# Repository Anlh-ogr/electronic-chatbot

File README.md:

# electronic-chatbot
chatbot AI

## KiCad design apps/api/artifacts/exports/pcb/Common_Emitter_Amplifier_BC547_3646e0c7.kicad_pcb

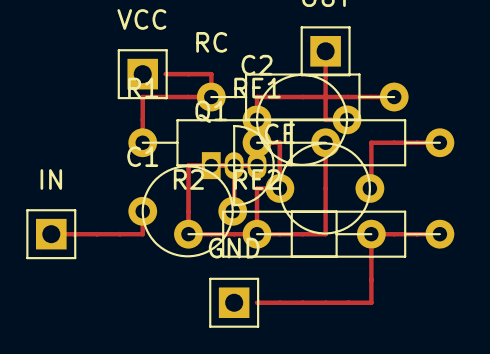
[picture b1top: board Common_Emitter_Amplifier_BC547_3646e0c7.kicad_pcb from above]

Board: 2 copper layers, 13 parts (0 on the bottom side), 8 nets.

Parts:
C1, C2: CAPACITOR; C_Disc_D5.0mm
CE: CAPACITOR; C_Disc_D5.0mm
GND: POWER_SYMBOL; N/A
IN: CONNECTOR; PinHeader_1x01_P2.54mm_Vertical
OUT: CONNECTOR; PinHeader_1x01_P2.54mm_Vertical
Q1: BJT_NPN; TO-92_Inline
R1, R2: RESISTOR; R_Axial_DIN0207
RC: RESISTOR; R_Axial_DIN0207
RE1, RE2: RESISTOR; R_Axial_DIN0207
VCC: POWER_SYMBOL; N/A

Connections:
0: GND.1, R2.2, RE2.2
BASE: C1.2, Q1.2, R1.2, R2.1
COLLECTOR: C2.1, Q1.3, RC.2
EMITTER: CE.1, Q1.1, RE1.1, RE2.1
IN: C1.1, IN.1
OUT: C2.2, OUT.1
RE_GND: CE.2, RE1.2
VCC: R1.1, RC.1, VCC.1

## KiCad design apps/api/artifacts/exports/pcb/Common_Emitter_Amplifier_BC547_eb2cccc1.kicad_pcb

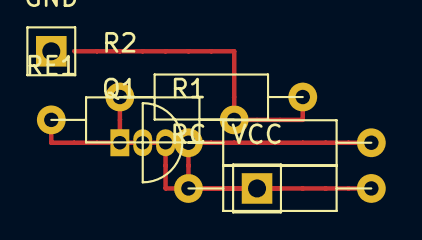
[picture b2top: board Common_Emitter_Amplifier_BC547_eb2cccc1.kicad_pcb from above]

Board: 2 copper layers, 7 parts (0 on the bottom side), 5 nets.

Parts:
GND: POWER_SYMBOL; None
Q1: BJT_NPN; TO-92_Inline
R1, R2: RESISTOR; R_Axial_DIN0207_L6.3mm_D2.5mm_P10.16mm_Horizontal
RC: RESISTOR; R_Axial_DIN0207_L6.3mm_D2.5mm_P10.16mm_Horizontal
RE1: RESISTOR; R_Axial_DIN0207_L6.3mm_D2.5mm_P10.16mm_Horizontal
VCC: POWER_SYMBOL; None

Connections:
0: GND.1, R2.2, RE1.2
BASE: Q1.2, R1.2, R2.1
COLLECTOR: Q1.3, RC.2
EMITTER: Q1.1, RE1.1
VCC: R1.1, RC.1, VCC.1

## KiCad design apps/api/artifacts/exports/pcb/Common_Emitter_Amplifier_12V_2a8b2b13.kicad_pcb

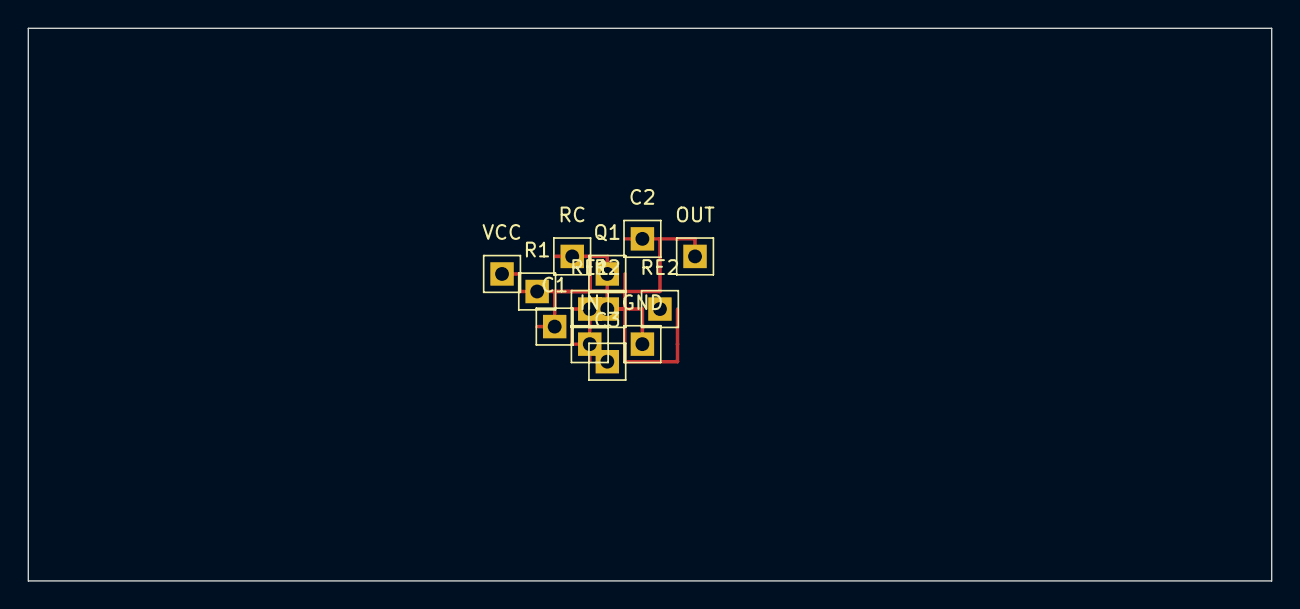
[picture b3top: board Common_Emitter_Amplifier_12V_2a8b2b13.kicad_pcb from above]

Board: 2 copper layers, 90.0 x 40.0 mm, 13 parts (0 on the bottom side), 4 nets.

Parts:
C1, C2, C3: CONNECTOR; PinHeader_1x01_P2.54mm_Vertical
GND: CONNECTOR; PinHeader_1x01_P2.54mm_Vertical
IN: CONNECTOR; PinHeader_1x01_P2.54mm_Vertical
OUT: CONNECTOR; PinHeader_1x01_P2.54mm_Vertical
Q1: CONNECTOR; PinHeader_1x01_P2.54mm_Vertical
R1, R2: CONNECTOR; PinHeader_1x01_P2.54mm_Vertical
RC: CONNECTOR; PinHeader_1x01_P2.54mm_Vertical
RE1, RE2: CONNECTOR; PinHeader_1x01_P2.54mm_Vertical
VCC: CONNECTOR; PinHeader_1x01_P2.54mm_Vertical

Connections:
BASE: R1.1, R2.1
IN: C1.1, IN.1
RE_NODE: C3.1, RE2.1
VCC: RC.1, VCC.1

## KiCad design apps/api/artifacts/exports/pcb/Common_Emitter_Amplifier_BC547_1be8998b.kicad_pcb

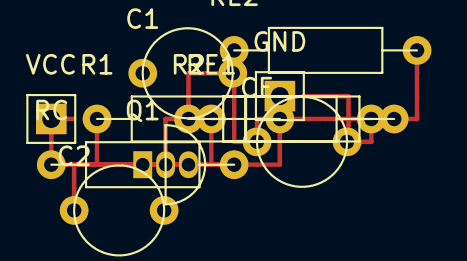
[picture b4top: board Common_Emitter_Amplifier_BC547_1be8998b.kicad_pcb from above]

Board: 2 copper layers, 11 parts (0 on the bottom side), 6 nets.

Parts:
C1, C2: CAPACITOR; C_Disc_D5.0mm
CE: CAPACITOR; C_Disc_D5.0mm
GND: POWER_SYMBOL; N/A
Q1: BJT_NPN; TO-92_Inline
R1, R2: RESISTOR; R_Axial_DIN0207
RC: RESISTOR; R_Axial_DIN0207
RE1, RE2: RESISTOR; R_Axial_DIN0207
VCC: POWER_SYMBOL; N/A

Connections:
0: CE.2, GND.1, R2.2, RE2.2
+12V: R1.2, RC.1, VCC.1
BASE: C1.2, Q1.2, R1.1, R2.1
COLLECTOR: C2.1, Q1.3, RC.2
EMITTER: Q1.1, RE1.1
RE_NODE: CE.1, RE1.2, RE2.1

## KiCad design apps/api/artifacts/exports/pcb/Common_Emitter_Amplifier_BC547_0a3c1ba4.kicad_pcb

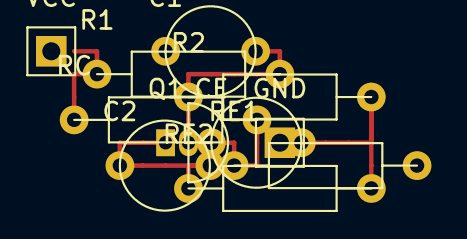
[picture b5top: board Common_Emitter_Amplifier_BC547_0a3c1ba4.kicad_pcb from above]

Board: 2 copper layers, 11 parts (0 on the bottom side), 5 nets.

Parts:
C1, C2: CAPACITOR; C_Disc_D5.0mm_W2.5mm_P5.00mm
CE: CAPACITOR; C_Disc_D5.0mm_W2.5mm_P5.00mm
GND: POWER_SYMBOL; N/A
Q1: BJT_NPN; TO-92_Inline
R1, R2: RESISTOR; R_Axial_DIN0207_L6.3mm_D2.5mm_P10.16mm_Horizontal
RC: RESISTOR; R_Axial_DIN0207_L6.3mm_D2.5mm_P10.16mm_Horizontal
RE1, RE2: RESISTOR; R_Axial_DIN0207_L6.3mm_D2.5mm_P10.16mm_Horizontal
VCC: POWER_SYMBOL; N/A

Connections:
0: CE.2, GND.1, R2.2, RE2.2
BASE: C1.2, Q1.2, R1.2, R2.1
COLLECTOR: C2.1, Q1.1, RC.2
EMITTER: CE.1, Q1.3, RE1.1, RE2.1
VCC: R1.1, RC.1, VCC.1

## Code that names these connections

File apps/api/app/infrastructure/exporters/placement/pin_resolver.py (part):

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#   Body half-length = 2.54 mm + 1 pin-stub (2.54 mm) → total = 5.08 mm
PIN_OFFSET: float = 2.0 * GRID_MM   # 5.08 mm (2 grid units)

# BJT pin distances:  base lateral (2 grid), collector/emitter vertical (2 grid)
BJT_BASE_OFFSET: float = 2.0 * GRID_MM   # 5.08 mm left for base
BJT_CE_OFFSET:   float = 2.0 * GRID_MM   # 5.08 mm up/down for C / E

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
def resolve_pins(comp_type: str, rotation: int = 0) -> Dict[str, Tuple[float, float]]:
    """Return pin offsets for a component type, applying rotation."""
    base = _fuzzy_pin_base(comp_type)
    if rotation % 360 == 0:
        return dict(base)
    return rotate_offsets(base, rotation)
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
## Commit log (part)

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2025-12-19 Refactor script to use CircuitStore default path
    Updated the script to instantiate CircuitStore without specifying a file path, relying on its default behavior. Also removed the unused variable 'db' for cleaner code.
2025-12-22 Add Pydantic schemas for chat request and response
    Introduces ChatRequest and ChatResponse models using Pydantic for validating and structuring chat API input and output data.
2025-12-23 Refactor chat endpoint and add circuits listing route
    Refactored the /chat endpoint to use CircuitStore directly, improved error handling, and clarified response structure. Added a new /circuits GET endpoint to list all circuits in the database.
2025-12-25 Refactor CircuitStore for improved clarity and config usage
    Refactored CircuitStore to use centralized config for the default database path, added type hints, improved comments, and enhanced metadata retrieval to include the 'project' field. The class now pro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
2025-12-29 Không commit file env.local
2025-12-30 Tạo một đầu nối API gọi các router từ thư mục
    Test với endpoind (health)
2026-01-07 Tập trung vào cấu trúc "Phân tầng Domain"
    Cập nhật định nghĩa Component, Net, Port và Constraint để phục vụ Rule Engine.
    Sử dụng Enums cho ComponentType và PortDirection để loại bỏ lỗi typo (magic strings).
    Triển khai phương thức with_component theo phong cách functional để hỗ trợ cập nhật mạch mà không thay đổi object cũ.
    Thêm ràng buộc kiểu dữ liệu ParameterValue để kiểm soát thông số linh kiện.
2026-01-11 Thêm tài liệu tổng quan hệ thống domain
    Bổ sung file docs/domain/tong-quan.md mô tả kiến trúc, điểm mạnh/yếu, quy trình kiểm thử, lộ trình phát triển và hướng dẫn sử dụng cho hệ thống domain circuits. Tài liệu giúp tổng hợp trạng thái hiện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
2026-01-11 Thêm tài liệu cho các thực thể domain mạch điện
    Giới thiệu một tài liệu Markdown chi tiết mô tả thiết kế, cấu trúc và logic kiểm định của tệp `entities.py` trong miền mạch điện. Tài liệu này bao gồm mục đích, mục tiêu, cấu trúc, vai trò và đánh gi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
2026-01-11 Thêm các bài kiểm tra toàn diện cho các mô-đun miền mạch
    Giới thiệu các bộ kiểm thử mới bao gồm các trường hợp ngoại lệ, tuần tự hóa/giải tuần tự hóa IR, đánh giá công cụ quy tắc và trình tạo mẫu tham số cho các thực thể mạch. Các bài kiểm thử này giúp tăn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
2026-01-19 thu vien hien thi mach kicanvas
    thu vien ho render tren web interface
2026-01-24 Mở rộng và làm rõ tài liệu IR cho lĩnh vực mạch điện
    Tài liệu IR (Intermediate Representation) cho lĩnh vực mạch điện đã được mở rộng và tái cấu trúc đáng kể.
    Bản cập nhật bổ sung các giải thích chi tiết về mục đích của IR, xác thực lược đồ, tính bất biến, kiểm thử khứ hồi và phân tách các mối quan tâm.
    Nó cũng bao gồm lý do kiến ​​trúc, điểm mạnh, hạn chế và các ví dụ sử dụng để cải thiện sự rõ ràng cho các nhà phát triển và người bảo trì.
2026-02-09 gỡ bản cũ
2026-02-11 Hỗ trợ kênh p và tái cấu trúc tính toán MOSFET
    Thêm hỗ trợ channel_type và tái cấu trúc các hàm hỗ trợ tính toán MOSFET.
    Giới thiệu MOSFETConfig.channel_type ("n"/"p"), thay đổi API MOSFETCalculator để trả về ParameterValue (có đơn vị) và chấp nhận ParameterValue cho đầu vào điện trở/tụ điện.
    Các phép tính hiện xử lý dấu/cực tính cho các thiết bị kênh p, sử dụng giá trị tuyệt đối để chuẩn hóa và mở rộng kiểm tra lỗi (kiểm tra tối thiểu VDS và xác thực độ lệch cổng).
    Đổi tên/tái cấu trúc logic xây dựng mạch (_create_nets -> _compute_values) để t
2026-02-18 Nâng cấp công cụ xử lý rules: mức độ nghiêm trọng & các hàm hỗ trợ
    Thêm các mức độ nghiêm trọng phong phú hơn và tái cấu trúc cơ sở hạ tầng quy tắc cơ bản để tăng tính mạnh mẽ và khả năng tái sử dụng.
    Mức độ nghiêm trọng của vi phạm (ViolationSeverity) có thêm mức ĐẠT THÀNH CÔNG (SUCCESS); Quy tắc mạch (CircuitRule) trở thành một quy tắc cơ bản trừu tượng (ABC) với cờ được bật, mô tả, validate_saf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
2026-02-22 sửa cmt
2026-03-11 cap nhat API
    Cập nhật tệp requirements.txt để sửa đổi các phụ thuộc API.
2026-03-12 Thêm các tệp siêu dữ liệu mẫu op-amp
    Thêm 13 tệp siêu dữ liệu op-amp mới (OP-01 đến OP-13) vào thư mục templates metadata.
    Mỗi tệp (metadata version v3.0.0) mô tả tham chiếu mẫu vật lý, phân loại miền (đảo, không đảo, vi sai; nguồn đơn/kép; tham chiếu AC/ảo/biến thể IO), cấu trúc chức năng (cổng, khối, công thức khuếch đ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
    Các mục siêu dữ liệu này cung cấp cho trình lập kế hoạch/giải quyết các chữ ký cấu trúc liên kết và gợi ý về kích th
2026-03-15 file init application
2026-03-19 Trình xác thực ràng buộc mạch
    Giới thiệu một Constraint Validator dựa trên quy tắc, có tính xác định để xác thực dữ liệu mạch được tạo ra.
    Thêm các lớp dữ liệu Violation và Validation Report và triển khai các kiểm tra cấu trúc, phạm vi tham số, khớp ý định và ràng buộc cứng (với mức độ nghiêm trọng lỗi/cảnh báo).
    Bao gồm các phạm vi tham số được xác định trước cho các thành phần phổ biến (điện trở, tụ điện, cuộn cảm, nguồn điện áp), tổng hợp các vi phạm và checked_rules, và trả về ValidationReport đạt/không đ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
    Được thiết k
2026-03-20 Tái cấu trúc bộ định tuyến LLM cho Google Cloud Gemini
    Tái cấu trúc lớn bộ định tuyến LLM: hợp nhất các vai trò thành một vai trò CHUNG, đơn giản hóa việc xử lý chế độ (AIR/PRO) và làm cho bộ định tuyến tập trung vào Gemini/Google Cloud.
    Thay thế mã và máy khách dành riêng cho Groq bằng logic tập trung vào GoogleCloud/Gemini, cập nhật việc phân giải biến môi trường (chấp nhận Google_Cloud_API_Key / GOOGLE_CLOUD_API_KEY / GEMINI_API_K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
    Hợp lý hóa việc xây dựng cấu h
2026-03-20 Thêm GenerateCircuitUseCase để tạo mẫu mạch
    Giới thiệu một trường hợp sử dụng mới để tạo mạch từ các mẫu.
    Thêm GenerateCircuitUseCase điều phối việc tải mẫu, xác thực tham số (ParameterValidator), ánh xạ tham số sang thành phần, xây dựng mạch thông qua TemplatesLoader, lưu trữ tùy chọn thông qua CircuitR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
    Đồng thời thêm enum TopologyType, xử lý lỗi mạnh mẽ (TemplateGenerationError) và chuyển đổi sang DTO CircuitResponse với siêu dữ liệu và thẻ.
    Hỗ trợ tìm kiếm mẫu gần đúng, cảnh báo về các vấ
2026-03-21 Thêm trình ánh xạ CircuitSpec
    Giới thiệu CircuitSpecMapper để chuyển đổi JSON CircuitSpec thành các thực thể Circuit trong miền và ngược lại.
    Thêm các hàm from_json/from_file/to_json và các hàm hỗ trợ để ánh xạ các thành phần, tham số, mạng và cổng, với chức năng xác thực, chuyển đổi kiểu (ComponentType, PortDirection), phân tích cú pháp P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
    Khóa các thành phần/mạng/cổng vào các từ điển thân thiện với miền và tuần tự hóa các thực thể thành JSON đặc tả.
2026-03-21 Xuất XGBoostTopologySelector trong gói ai_core
    Nhập XGBoostTopologySelector trong apps/api/app/domains/circuits/ai_core/__init__.py và thêm nó vào __all__ để bộ chọn được xuất công khai từ gói ai_core cho mục đích sử dụng bên ngoài.
2026-03-21 Trình kết xuất SVG cho KiCad CLI
    Giới thiệu KiCadCLIRenderer để kết xuất sơ đồ/PCB KiCad sang SVG bằng công cụ kicad-cli.
    Cung cấp các phương thức kết xuất bất đồng bộ và đồng bộ (render_to_svg / render_to_svg_sync), tìm kiếm các vị trí cài đặt phổ biến hoặc PATH cho kicad-cli, quản lý thư mục đầu ra, ghi nhật ký thực t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
    Được thiết kế như một phương án dự phòng phía máy chủ khi API KiCad trực tiếp hoặc kết xuất trình duyệt không khả dụng; yêu cầu kicad-cli phải được cài đặt trê
2026-03-21 Thêm kho lưu trữ mạch trong bộ nhớ
    Giới thiệu InMemoryCircuitRepository triển khai CircuitRepositoryPort (apps/api/.../circuits_repo_memory.py).
    Lưu trữ các thực thể Mạch trong một từ điển với các phương thức bất đồng bộ: lưu (tạo UUID nếu thiếu), lấy, liệt kê (hỗ trợ lọc tên đơn giản, phân trang và sắp xếp cơ bản), cập nhật, xóa, đếm và xóa 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
    Dành cho phát triển, thử nghiệm và MVP (không dành cho sản xuất); sử dụng ghi nhật ký và các phần giữ chỗ cho các cải tiến khóa/siêu dữ liệu trong tương lai.
2026-03-21 Khởi tạo ứng dụng FastAPI, thêm các tuyến routes
    Tái cấu trúc điểm vào chính của FastAPI: mở rộng chuỗi tài liệu mô-đun, thêm/nhập các bộ định tuyến cho chatbot, mạch và ảnh chụp nhanh, và đăng ký chúng trên ứng dụng.
    Giới thiệu SafeStaticFiles để trả về lỗi 404 cho các tệp tĩnh bị thiếu thay vì lỗi 500. Thêm các điểm cuối đơn giản: /api/health (kiểm tra trạng thái), / (phục vụ trang index.html phía giao diện ngườ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
    Đồng thời điều chỉnh các phần nhập
2026-03-21 Thêm mã JavaScript giao diện người dùng chatbot cho trợ lý mạch điện
    Giới thiệu một tập lệnh giao diện người dùng mới apps/api/static/js/chatbot.js triển khai giao diện người dùng và logic của Chatbot mạch điện tử.
    Các tính năng bao gồm: xử lý tin nhắn trò chuyện, kiểm tra trạng thái API, gửi/truyền yêu cầu mô phỏng (/api/chat, /api/chat/simulate/stream), phân tích luồng kiểu SSE, xây dựng danh sách mạng từ dữ 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
2026-03-22 NLU: phân tích độ khuếch đại, trở kháng đầu ra, ghép nối trực tiếp
    Cải thiện khả năng phân tích cú pháp của NLUService để phát hiện các yêu cầu bổ sung từ văn bản người dùng.
    Thêm các mẫu output_buffer bổ sung (các cụm từ trở kháng đầu ra thấp bằng tiếng Việt và tiếng Anh).
    Triển khai phân tích phạm vi độ khuếch đại (ví dụ: "gain 20-30", các biến thể tiếng Việt) và lưu trữ gain_min/gain_max.
    Thêm phân tích giới hạn trở kháng đầu ra (zout/trở kháng đầu ra) và lưu trữ output_impedance_max_ohm.
    Thêm tính năng phát hiện yêu cầu bắt buộc về g
2026-03-22 Sử dụng hình ảnh avatar bot
    Thay thế biểu tượng robot Font Awesome bằng hình ảnh tùy chỉnh cho avatar bot trong giao diện người dùng chatbot.
    Thay đổi này sẽ hoán đổi `<i class="fas fa-robot"></i>` với `<img src="/static/logo/System-icon.png" alt="Bot Avatar">` trong addMessage và chỉ báo đang nhập (showTyping), cải thiện tính nhất quán về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
2026-03-27 Thêm tập lệnh huấn luyện RF cho cấu trúc liên kết và khối
    Thêm một tập lệnh huấn luyện mới apps/api/resources/ml/train_rf_topology_block.py để xây dựng và lưu hai mô hình RandomForest nhằm dự đoán họ cấu trúc liên kết và loại khối chính. Tập lệnh tải siêu d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
2026-03-27 Thêm trình kiểm tra độ lệch DC ở cấp độ miền
    Giới thiệu trình kiểm tra độ lệch DC ở cấp độ miền (apps/api/app/domain/validators/dc_bias_validator.py). Thêm các lớp dữ liệu ComponentSet và DCValidationResult và một DCBiasValidator với các phương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
2026-03-27 Thêm bộ chọn mô hình và chế độ gửi tin nhắn
    Giới thiệu menu thả xuống chọn mô hình và truyền cấp độ mô hình đã chọn qua các yêu cầu trò chuyện và giao diện người dùng. Thêm các tham chiếu DOM và setupModelDropdown() để quản lý việc mở/đóng, lự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
2026-04-15 Thêm các schematic và SVG debug_matrix cho KiCad
    Bổ sung các artifact mạch debug_matrix: thêm các schematic KiCad cho các mạch khuếch đại BJT (bjt_cb, bjt_cc, bjt_ce) và các ví dụ op-amp (opamp_diff, opamp_inv, opamp_noninv), kèm theo các ảnh SVG p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
    Các schematic bao gồm metadata như BOM/title và các annotation cho connector/port (VIN, VOUT, VCC, GND), được sinh tự động bởi generator electronic-chatbot.
2026-04-16 Điều chỉnh các repository theo schema Neon (sessions/snapshots)
    Di chuyển các repository để tương thích với schema và cách hoạt động của Neon:
    1. chat_context_repository:
    - Sử dụng SessionModel, cập nhật session.last_active khi thao tác chat/message.
    - Tạo chat gắn với session, kiểm tra tồn tại chat khi tạo message.
    - Thêm get_message và update_message_content.
    - Đồng bộ timestamp bằng một giá trị thời gian duy nhất.
2026-04-19 image result
2026-04-20 update requirement
